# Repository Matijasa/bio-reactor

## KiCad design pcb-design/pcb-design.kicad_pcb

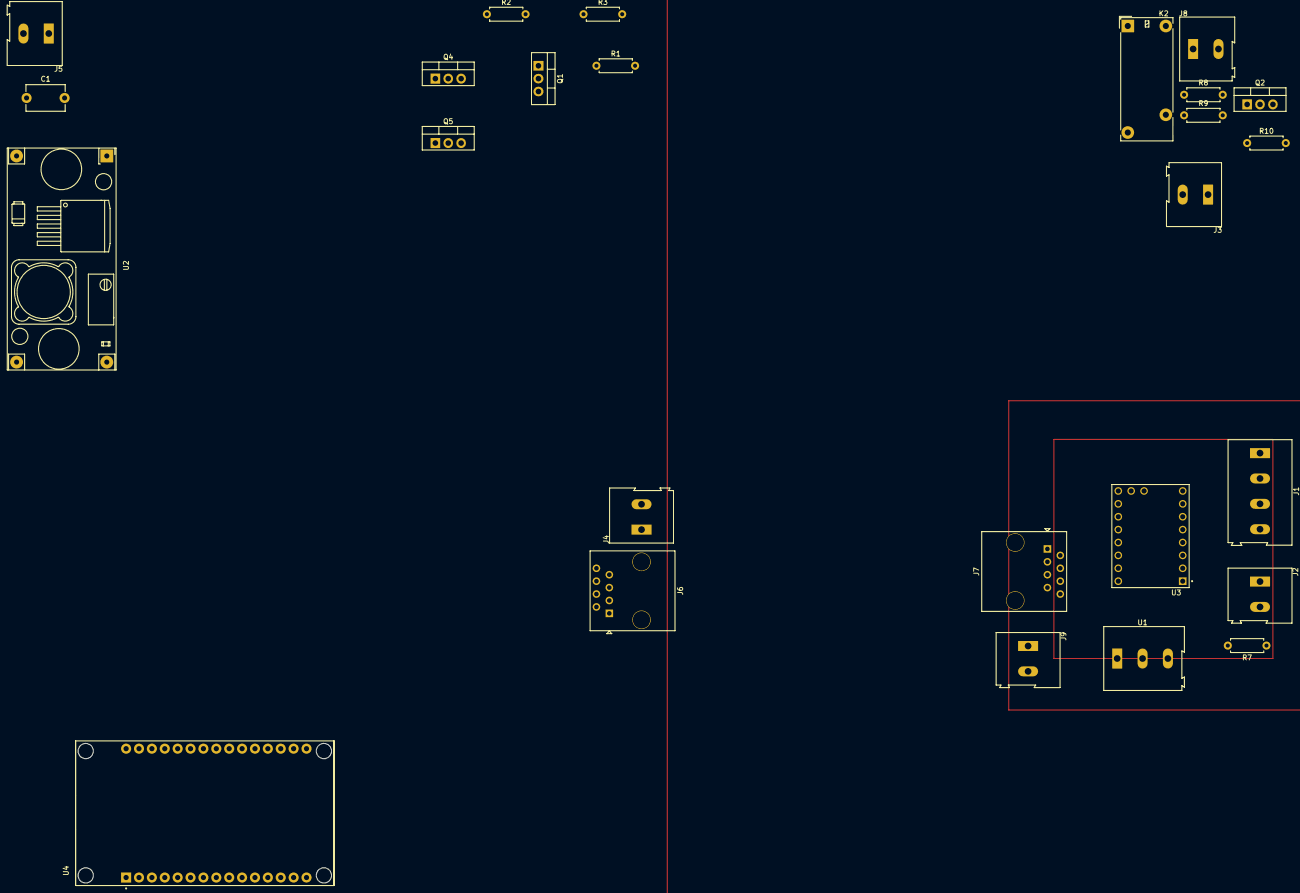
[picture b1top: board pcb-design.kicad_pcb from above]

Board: 2 copper layers, 26 parts (0 on the bottom side), 27 nets, no tracks yet.

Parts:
C1: C 16V 100nF; C_Disc_D7.5mm_W5.0mm_P7.50mm
J1: Screw_Terminal_Motor; TerminalBlock_Altech_AK300-4_P5.00mm
J2: Screw_Terminal_Heater; TerminalBlock_Altech_AK300-2_P5.00mm
J3: Screw_Terminal_AC_Power; TerminalBlock_Altech_AK300-2_P5.00mm
J4: Power_transfer_cable_main; TerminalBlock_Altech_AK300-2_P5.00mm
J5: Screw_Terminal_DC_Power; TerminalBlock_Altech_AK300-2_P5.00mm
J6: rj45_main; RJ45_OST_PJ012-8P8CX_Vertical
J7: RJ45; RJ45_OST_PJ012-8P8CX_Vertical
J8: Screw_Terminal_Bubler; TerminalBlock_Altech_AK300-2_P5.00mm
J9: Power_transfer_cable_slave; TerminalBlock_Altech_AK300-2_P5.00mm
K2: ADW11; Relay_1P1T_NO_10x24x18.8mm_Panasonic_ADW11xxxxW_THT
Q1: IRF3205_heater; TO-220-3_Vertical
Q2: IRF3205_bubler; TO-220-3_Vertical
Q4, Q5: MT3203_heater; TO-220-3_Vertical
R1: 2k2; R_Axial_DIN0207_L6.3mm_D2.5mm_P7.62mm_Horizontal
R2: 100; R_Axial_DIN0207_L6.3mm_D2.5mm_P7.62mm_Horizontal
R3, R8, R9, R10: 10k; R_Axial_DIN0207_L6.3mm_D2.5mm_P7.62mm_Horizontal
R7: 4k7; R_Axial_DIN0207_L6.3mm_D2.5mm_P7.62mm_Horizontal
U1: temperature sensor; TerminalBlock_Altech_AK300-3_P5.00mm
U2: step_down_converter; YAAJ_DCDC_StepDown_LM2596
U3: TMC2209_stepper_driver; MODULE_TMC2209_SILENTSTEPSTICK
U4: ESP32-DEVKIT-V1; MODULE_ESP32_DEVKIT_V1

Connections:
+3.3V: R7.1, U1.3 (V_{DD}), U2.4 (Vout), U3.2 (VIO), U4.30 (VIN)
+12V: C1.2, J2.2, J5.1, R3.1, R9.1, U2.1 (Vin), U3.8 (VM)
/Bubler driver circuit/^signal_bubler_enable: Q2.1 (G), R10.1
/^signal_heater: Q1.1 (G), R1.1
/signal_temp_probe: J6.1, J7.1, R7.2, U1.2 (DQ), U4.19 (D34)
AC: J3.2, K2.5
Earth: J3.1, J8.1
GND: C1.1, J5.2, K2.1, Q1.3 (S), Q2.3 (S), Q4.3 (S), Q5.3 (S), R1.2, R10.2, U1.1 (GND), U2.2 (GND), U2.3 (GND), U3.1 (GND), U3.7 (GND), U3.16 (~EN), U4.2 (GND), U4.29 (GND)
unnamed: J1.1, U3.4 (M1A)
unnamed: J1.2, U3.5 (M2A)
unnamed: J1.3, U3.3 (M1B)
unnamed: J1.4, U3.6 (M2B)
unnamed: J2.1, Q4.2 (D), Q5.2 (D)
unnamed: J4.1, J9.1
unnamed: J4.2, J9.2
unnamed: J6.4, J7.4
unnamed: J6.5, J7.5
unnamed: J6.6, J7.6
unnamed: J6.7, J7.7
unnamed: J6.8, J7.8
unnamed: J8.2, K2.3
unnamed: K2.6, R8.2
unnamed: Q1.2 (D), R2.1, R3.2
unnamed: Q2.2 (D), R8.1, R9.2
unnamed: Q4.1 (G), Q5.1 (G), R2.2
signal_uart_rx: J6.3, J7.3, U3.12 (UART), U4.21 (D32)
signal_uart_tx: J6.2, J7.2, U3.13 (SPRD), U4.25 (D27)

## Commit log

2022-09-16 basic website doc
2022-09-17 Working styled markdown to web generation. Support for code highliting and mathjax latex rendering
2022-09-17 deploy fix
2022-09-18 mobile fix
2022-09-18 readme link
2022-09-18 inline code render fix
2022-09-18 simple header added
2022-09-26 Start of the documentation and test deploy
2022-09-28 prints added
2022-10-27 dodajanje
2022-10-27 test spremembe index.md
2023-02-17 dodajanje Freecad delov
2023-02-18 deleted lid2 plus made rod holders
    pogledi ce ti je kul oz bova jutre extra delala in printala
2023-02-18 updated lid model
    popravu izgled lukne so ble mal mutave
2023-02-18 big update kosov
2023-02-18 redo
2023-02-21 bubbler dizajn
2023-02-22 bubbler update
2023-02-23 bubbler
2023-02-26 babler apdejt
2023-02-26 bubbler improved
2023-03-23 added some text
2023-03-24 added arduino folder
2023-03-24 pcb desing folder
2023-03-25 random ardo stuff
2023-03-27 added text also fixed pic display
2023-03-30 text
2023-03-30 image fix
2023-04-11 test
2023-04-14 added photos
2023-06-28 schematic
2023-08-09 design
2023-08-10 updated models
2023-08-11 updated motor code
2023-08-20 tests and corrections on final circuits
2023-11-11 divided pcs
2023-11-11 nek updejt kosov
2023-11-11 posodobitev kosov
2024-06-29 motor test
2024-06-29 [#2] Updated cpp
2024-06-29 dela vse na motorju
2024-06-30 new axel adapter desing
2024-07-11 designs
2026-01-03 Changed text on index.md and added one pic
2026-01-05 added some text and trwo pitures
2026-01-05 pre deploy
2026-01-05 lan ready
2026-01-06 compressed videos for deployment
2026-01-06 retry
2026-01-12 Some text updates and an added picture
2026-01-12 fixed int to unsigned
